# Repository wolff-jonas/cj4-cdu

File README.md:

# Overview

This is a physical button box in the rough shape and functionality of the CDU of the Citation CJ4.
It is primarily intended for use with Microsoft Flight Simulator 2020, but could be adapted to other simulators (or planes) as well.

For more indepth information head over to: https://jwolff.it/cj4-cdu/

## Hardware 

It's constructed with a 3D printed front plate, 3D printed keys, a custom PCB and an Arduino Mega.

The CAD for the front plate, and the 3 different kinds of keys are in CAD/ folder.
The is only one key for each type. For the whole keyboard you would have to copy and modify them with the labeling.

The schematics and design files for the PCB are in the kicad/ folder.

> [!CAUTION]
> If you plan on using the PCB: __triple check the footprints__ of the buttons!
>
> The buttons I ordered had different footprints. I had manually rework all the ground wires to make it work.
> I did __not__ update the PCB.

## Software

This uses [Mobiflight](https://www.mobiflight.com) for sending the correct key events to the sim.
Make sure you have the WASM module installed and downloaded the CJ4 Preset from HubHop.

The configs file mobiflight are in the mobiflight/ folder.

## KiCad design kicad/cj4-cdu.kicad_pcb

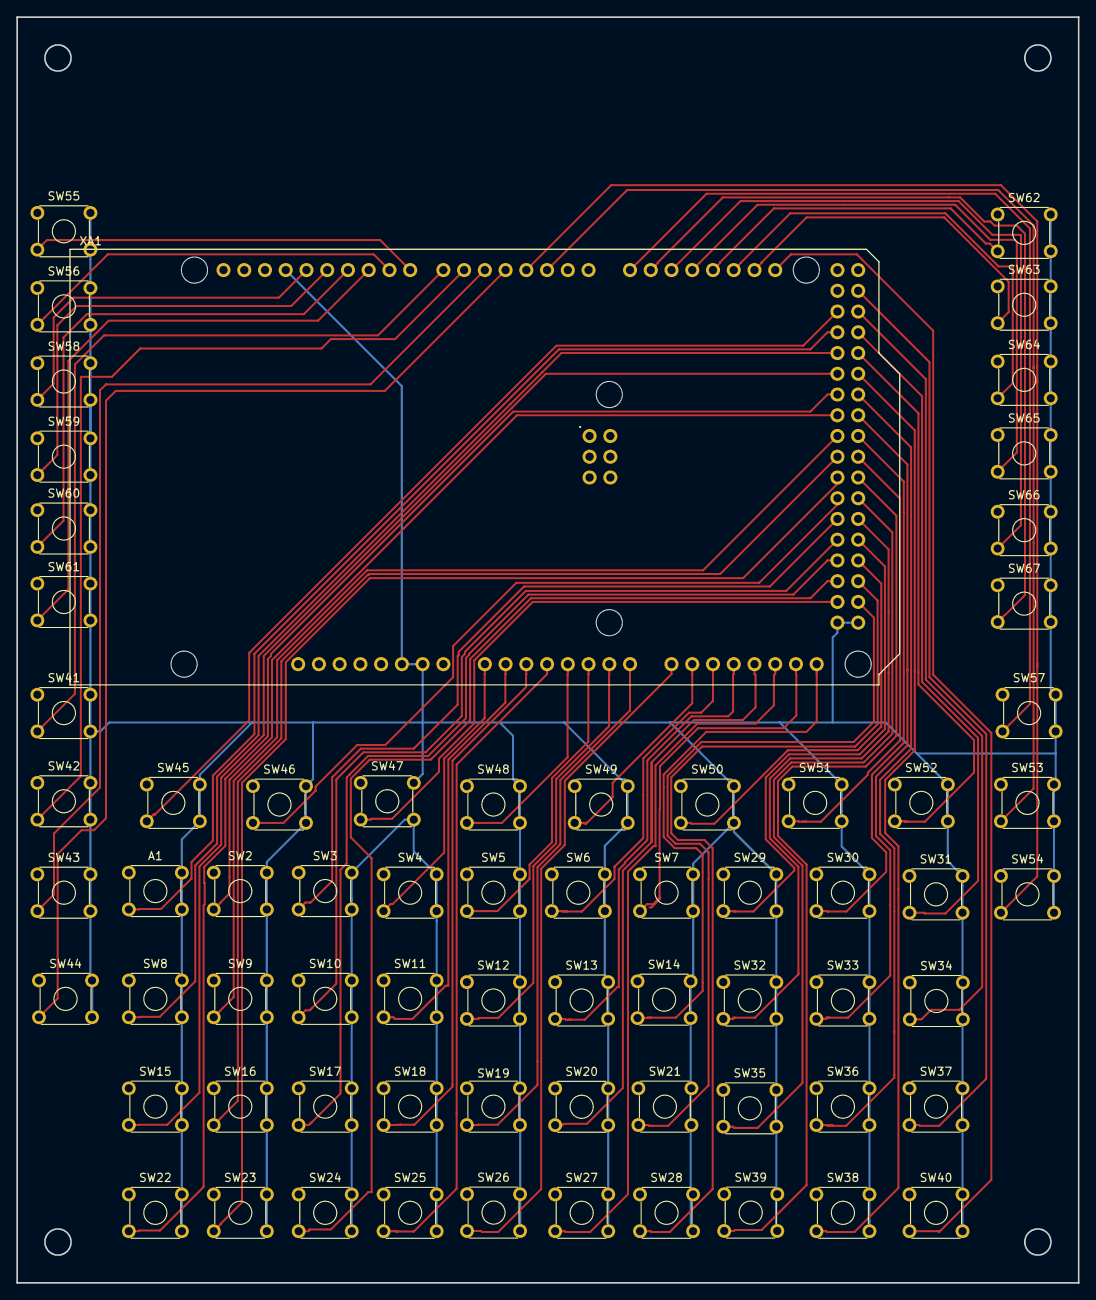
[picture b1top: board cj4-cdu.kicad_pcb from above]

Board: 2 copper layers, 130.0 x 155.0 mm, 68 parts (0 on the bottom side), 68 nets.

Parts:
A1: A; SW_TH_Tactile_Omron_B3F-10xx
SW2: B; SW_TH_Tactile_Omron_B3F-10xx
SW3: C; SW_TH_Tactile_Omron_B3F-10xx
SW4: D; SW_TH_Tactile_Omron_B3F-10xx
SW5: E; SW_TH_Tactile_Omron_B3F-10xx
SW6: F; SW_TH_Tactile_Omron_B3F-10xx
SW7: G; SW_TH_Tactile_Omron_B3F-10xx
SW8: H; SW_TH_Tactile_Omron_B3F-10xx
SW9: I; SW_TH_Tactile_Omron_B3F-10xx
SW10: J; SW_TH_Tactile_Omron_B3F-10xx
SW11: K; SW_TH_Tactile_Omron_B3F-10xx
SW12: L; SW_TH_Tactile_Omron_B3F-10xx
SW13: M; SW_TH_Tactile_Omron_B3F-10xx
SW14: N; SW_TH_Tactile_Omron_B3F-10xx
SW15: Q; SW_TH_Tactile_Omron_B3F-10xx
SW16: P; SW_TH_Tactile_Omron_B3F-10xx
SW17, SW18, SW19, SW20, SW21, SW22, SW23, SW24, SW25, SW26, SW27, SW28, SW29, SW30, SW31, SW32, SW33, SW34, SW35, SW36, SW37, SW38, SW39, SW40, SW41, SW42, SW43, SW44, SW45, SW46, SW47, SW48, SW49, SW50, SW51, SW52, SW53, SW54, SW55, SW56, SW57, SW58, SW59, SW60, SW61, SW62, SW63, SW64, SW65, SW66, SW67: SW_DPST; SW_TH_Tactile_Omron_B3F-10xx
XA1: Arduino_Mega2560_Shield

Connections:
/0: SW38.3, XA1.D31
/1: SW29.3, XA1.D47
/2: SW30.3, XA1.D37
/3: SW31.3, XA1.D27
/4: SW32.3, XA1.D45
/5: SW33.3, XA1.D35
/6: SW34.3, XA1.D25
/7: SW35.3, XA1.D43
/8: SW36.3, XA1.D33
/9: SW37.3, XA1.D23
/A: A1.3, XA1.D26
/B: SW2.3, XA1.D34
/C: SW3.3, XA1.D44
/CLRDEL: SW54.3, XA1.D3
/D: SW4.3, XA1.A0
/DEPARR: SW47.3, XA1.D52
/DIR: SW42.3, XA1.D6
/DOT: SW39.3, XA1.D41
/DSPLMENU: SW49.3, XA1.A9
/E: SW5.3, XA1.A5
/EXEC: SW57.3, XA1.D14
/F: SW6.3, XA1.A10
/FPLN: SW45.3, XA1.D24
/G: SW7.3, XA1.A14
/H: SW8.3, XA1.D28
/I: SW9.3, XA1.D36
/IDX: SW43.3, XA1.D5
/J: SW10.3, XA1.D46
/K: SW11.3, XA1.A1
/L: SW12.3, XA1.A6
/LEGS: SW46.3, XA1.D42
/LSK_L1: SW55.3, XA1.D8
/LSK_L2: SW56.3, XA1.D9
/LSK_L3: SW58.3, XA1.D13
/LSK_L4: SW59.3, XA1.D12
/LSK_L5: SW60.3, XA1.D11
/LSK_L6: SW61.3, XA1.D10
/LSK_R1: SW62.3, XA1.D18
/LSK_R2: SW63.3, XA1.D20
/LSK_R3: SW64.3, XA1.D19
/LSK_R4: SW65.3, XA1.D17
/LSK_R5: SW66.3, XA1.D16
/LSK_R6: SW67.3, XA1.D15
/M: SW13.3, XA1.A11
/MFDADV: SW50.3, XA1.D49
/MFDDATA: SW51.3, XA1.D39
/MSG: SW41.3, XA1.D7
/N: SW14.3, XA1.A15
/NEXT: SW53.3, XA1.D2
/O: SW15.3, XA1.D30
/P: SW16.3, XA1.D38
/PERF: SW48.3, XA1.A4
/PLUSMINUS: SW40.3, XA1.D21
/PREV: SW52.3, XA1.D29
/Q: SW17.3, XA1.D48
/R: SW18.3, XA1.A2
/S: SW19.3, XA1.A7
/SLASH: SW28.3, XA1.D51
/SP: SW27.3, XA1.A13
/T: SW20.3, XA1.A12
/TUN: SW44.3, XA1.D4
/U: SW21.3, XA1.D53
/V: SW22.3, XA1.D32
/W: SW23.3, XA1.D40
/X: SW24.3, XA1.D50
/Y: SW25.3, XA1.A3
/Z: SW26.3, XA1.A8
GND: A1.2, A1.4, SW2.2, SW2.4, SW3.2, SW3.4, SW4.2, SW4.4, SW5.2, SW5.4, SW6.2, SW6.4, SW7.2, SW7.4, SW8.2, SW8.4, SW9.2, SW9.4, SW10.2, SW10.4, SW11.2, SW11.4, SW12.2, SW12.4, SW13.2, SW13.4, SW14.2, SW14.4, SW15.2, SW15.4, SW16.2, SW16.4, SW17.2, SW17.4, SW18.2, SW18.4, SW19.2, SW19.4, SW20.2, SW20.4, SW21.2, SW21.4, SW22.2, SW22.4, SW23.2, SW23.4, SW24.2, SW24.4, SW25.2, SW25.4, SW26.2, SW26.4, SW27.2, SW27.4, SW28.2, SW28.4, SW29.2, SW29.4, SW30.2, SW30.4, SW31.2, SW31.4, SW32.2, SW32.4, SW33.2, SW33.4, SW34.2, SW34.4, SW35.2, SW35.4, SW36.2, SW36.4, SW37.2, SW37.4, SW38.2, SW38.4, SW39.2, SW39.4, SW40.2, SW40.4, SW41.2, SW41.4, SW42.2, SW42.4, SW43.2, SW43.4, SW44.2, SW44.4, SW45.2, SW45.4, SW46.2, SW46.4, SW47.2, SW47.4, SW48.2, SW48.4, SW49.2, SW49.4, SW50.2, SW50.4, SW51.2, SW51.4, SW52.2, SW52.4, SW53.2, SW53.4, SW54.2, SW54.4, SW55.2, SW55.4, SW56.2, SW56.4, SW57.2, SW57.4, SW58.2, SW58.4, SW59.2, SW59.4, SW60.2, SW60.4, SW61.2, SW61.4, SW62.2, SW62.4, SW63.2, SW63.4, SW64.2, SW64.4, SW65.2, SW65.4, SW66.2, SW66.4, SW67.2, SW67.4, XA1.GND1, XA1.GND2, XA1.GND3, XA1.GND5, XA1.GND6

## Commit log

2024-02-20 CAD, KiCad, Mobiflight and Images
2024-02-21 New CAD files and updated readme
